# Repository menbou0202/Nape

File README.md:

# Nape

Nape is a wireless trackball input device based on ZMK firmware.

## Files

- `case/`: STEP case files
- `doc/`: Documentation
- `pcb/`: KiCad 10 PCB design files, Gerber/drill files, and JLCPCB PCBA reference files

## Documentation

- [Build guide (Japanese)](doc/build-guide.md)

The firmware configuration is available at [menbou0202/zmk-config-nape](https://github.com/menbou0202/zmk-config-nape).

## License

- PCB design files in `pcb/` are licensed under `GPL-3.0-only`. See [`pcb/LICENSE`](pcb/LICENSE).
- Case design files in `case/` are licensed under `CERN-OHL-P-2.0`. See [`case/LICENSE`](case/LICENSE).

The PMW3610 circuit is derived from [kumamuk-git/roBa](https://github.com/kumamuk-git/roBa) and has been modified for Nape.

Before ordering a PCB or PCBA, read [`pcb/README.md`](pcb/README.md). In particular,
the placement of `BT1` in the supplied CPL was corrected manually for the
previous assembly order; do not replace it with an unreviewed KiCad export.

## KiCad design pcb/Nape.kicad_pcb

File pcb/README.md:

# PCB

Open `Nape.kicad_pro` with KiCad 10.

The project includes all symbols and custom footprints it references under
`libraries/`. The project-local `sym-lib-table` and `fp-lib-table` use
`${KIPRJMOD}`, so no global custom-library setup is required.

The PCB design files in this directory are licensed under `GPL-3.0-only`. See [`LICENSE`](LICENSE).

The PMW3610 circuit is derived from [kumamuk-git/roBa](https://github.com/kumamuk-git/roBa), licensed under GPL-3.0, and modified for Nape.

## Fabrication and assembly files

- `gerber/` contains the Gerber and plated/non-plated drill files exported in
  April 2025 for a previous PCB order. The board outline and drill coordinates
  match the current KiCad 10 design; KiCad 8 and 10 produce some differently ordered
  Gerber commands and aperture definitions.
- `pcba/Nape_bom.csv` and `pcba/Nape_cpl.csv` are the BOM and placement data
  from that order. They are JLCPCB ordering references, not a substitute for
  checking the current board and parts before a new order.

The `BT1` placement and rotation in the CPL were corrected manually for the
assembly order. **Do not replace this row with an unreviewed KiCad export.**
Check the assembly preview and component orientation before submitting any
new PCBA order.

The LCSC part numbers in the PMW3610 circuit are inherited from roBa and match
the JLCPCB-assembled configuration tested with Nape. Some LCSC part
specifications differ from the nominal values displayed in the schematic. In
particular, the BOM uses `C19666` for capacitors with several different
nominal values; verify the actual part specifications and availability before
reordering.

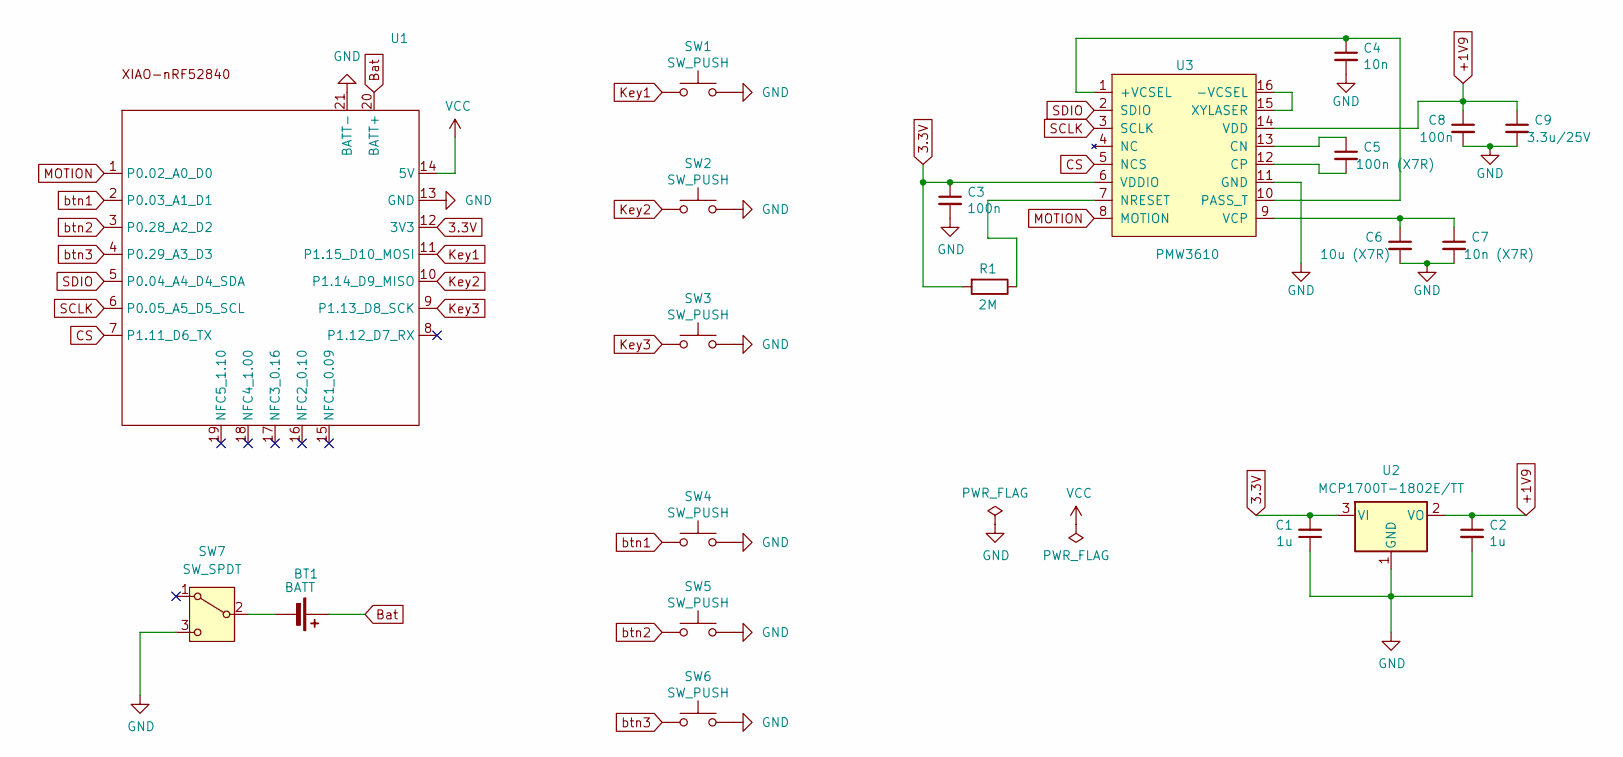
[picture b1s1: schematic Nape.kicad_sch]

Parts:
BT1: BATT; JST_S2B-PH-SM4-TB; LCSC C295747
C1: 1u; C_0603_1608Metric; LCSC C14663
C2: 1u; C_0603_1608Metric; LCSC C15849
C3, C8: 100n; C_0603_1608Metric; LCSC C19666
C4: 10n; C_0603_1608Metric; LCSC C19666
C5: 100n (X7R); C_0603_1608Metric; LCSC C19666
C6: 10u (X7R); C_0603_1608Metric; LCSC C19666
C7: 10n (X7R); C_0603_1608Metric; LCSC C19666
C9: 3.3u/25V; C_0603_1608Metric; LCSC C19666
R1: 2M; C_0603_1608Metric; LCSC C26102
SW1, SW2, SW3: SW_PUSH; Choc_v2_Hotswap_1u
SW4, SW5, SW6: SW_PUSH; ResetSW
SW7: SW_SPDT; TGSW_MSK-12D19
U1: XIAO_nRF52840_wBAT_wNFC_1
U2: MCP1700T-1802E/TT; SOT-23; LCSC C150796
U3: PMW3610; PMW3610DM-SUDU 16Pin

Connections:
3.3V: C1.2, C3.1, R1.2, U1.12 (3V3), U2.3 (VI), U3.6 (VDDIO)
+1V9: C2.1, C8.1, C9.1, U2.2 (VO), U3.14 (VDD)
Bat: BT1.1 (+), U1.20 (BATT+)
CS: U1.7 (P1.11_D6_TX), U3.5 (NCS)
GND: C1.1, C2.2, C3.2, C4.2, C6.2, C7.2, C8.2, C9.2, SW1.1, SW2.1, SW3.1, SW4.1, SW5.1, SW6.1, SW7.3 (C), U1.13 (GND), U1.21 (BATT-), U2.1 (GND), U3.11 (GND)
Key1: SW1.2, U1.11 (P1.15_D10_MOSI)
Key2: SW2.2, U1.10 (P1.14_D9_MISO)
Key3: SW3.2, U1.9 (P1.13_D8_SCK)
MOTION: U1.1 (P0.02_A0_D0), U3.8 (MOTION)
unnamed: BT1.2 (-), SW7.2 (B)
unnamed: C4.1, U3.1 (+VCSEL), U3.10 (PASS_T)
unnamed: U3.15 (XYLASER), U3.16 (-VCSEL)
unnamed: C5.1, U3.13 (CN)
unnamed: C5.2, U3.12 (CP)
unnamed: R1.1, U3.7 (NRESET)
unnamed: C6.1, C7.1, U3.9 (VCP)
SCLK: U1.6 (P0.05_A5_D5_SCL), U3.3 (SCLK)
SDIO: U1.5 (P0.04_A4_D4_SDA), U3.2 (SDIO)
VCC: U1.14 (5V)
btn1: SW4.2, U1.2 (P0.03_A1_D1)
btn2: SW5.2, U1.3 (P0.28_A2_D2)
btn3: SW6.2, U1.4 (P0.29_A3_D3)

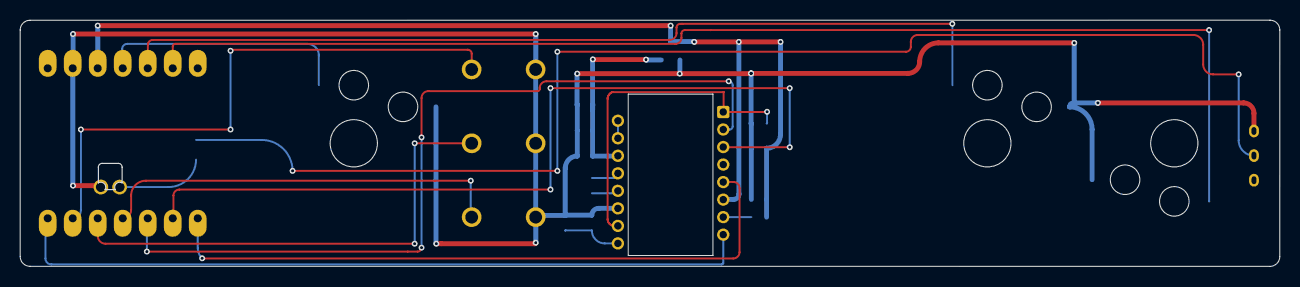
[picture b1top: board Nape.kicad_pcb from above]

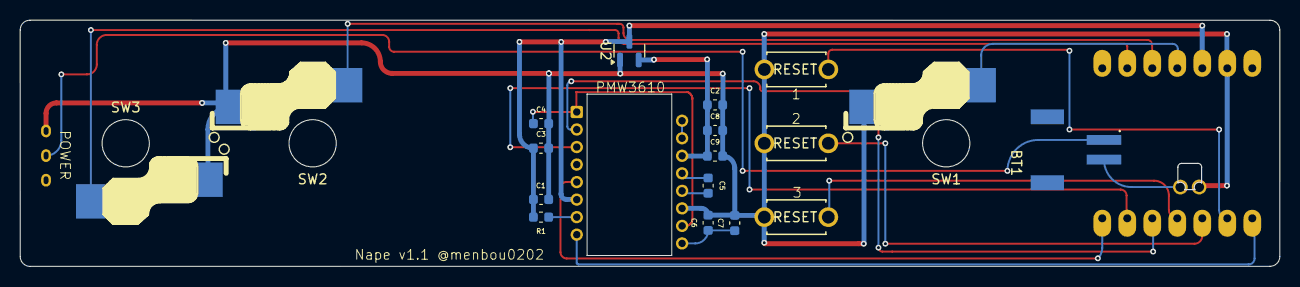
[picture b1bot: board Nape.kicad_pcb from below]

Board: 2 copper layers, 127.9 x 25.0 mm, 21 parts (17 on the bottom side), 21 nets.

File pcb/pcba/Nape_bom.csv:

Comment,Designator,Footprint,LCSC
MCP1700T-1802E/TT,U2,_kicad_footprints:SOT-23,C150796
BATT,BT1,_kicad_footprints:JST_S2B-PH-SM4-TB,C295747
3.3u/25V,C9,_kicad_footprints:C_0603_1608Metric,C19666
10u (X7R),C6,_kicad_footprints:C_0603_1608Metric,C19666
10n (X7R),C7,_kicad_footprints:C_0603_1608Metric,C19666
100n (X7R),C5,_kicad_footprints:C_0603_1608Metric,C19666
2M,R1,_kicad_footprints:C_0603_1608Metric,C26102
1u,C2,_kicad_footprints:C_0603_1608Metric,C15849
1u,C1,_kicad_footprints:C_0603_1608Metric,C14663
100n,"C3,C8",_kicad_footprints:C_0603_1608Metric,C19666
10n,C4,_kicad_footprints:C_0603_1608Metric,C19666
